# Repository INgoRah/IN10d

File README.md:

Arduino 1-Wire Homeautomation Base

# Changes
[x] timer based control (different switch table?). Use CLI sw t <bus> <adr> <latch> <bus> <adr> <pio>.
    Default 30 secs at the moment
[x] Host IF for switch table
[x] Host IF for control
[x] Host GPIO signal verified
[x] Switch with same dst does not clear timer if running.
[x] Log latch and switch

# Documentation

## Build
Create a post_extra_script.py to copy over to PI:
Import("env", "projenv")
env.AddPostAction(
    "$BUILD_DIR/${PROGNAME}.elf",
    env.VerboseAction(" ".join([
        "scp ",
        "$BUILD_DIR/${PROGNAME}.hex", "<user>@<ip>:<path>/${PROGNAME}.hex"
    ]), "Copying $BUILD_DIR/${PROGNAME}.hex")
)

Build using PlatformIO: %USERPROFILE%\.platformio\penv\Scripts\platformio.exe run --environment nanoatmega328-deploy

Debugging with "simulation" target

## Features Details

### Alarm handling

Each custom DS2408 generates an alarm signal of > 800 us on the OneWire line. No
other master supports detection of it. But this is a feature of the iButton.
Therefore I need a master to at least monitor the line and signal it to an
other master. The Arduino turned out to be fast and stable to handle basic
light switches in reasonable time compared to a Linux host (threads, updates,
script latency and overhead). So the Arduino controls the light switches.

### Address format and limitations

The adress scheme is aligned with the slave implementation to save space in
the Arduino Nano and speed up the lookup. Only bus and address needs to be known
(and detected in the alarm search).
The latch in the lookup table is only the latch number, no bitmap. Means pressing two
switches at the same time is ignored (first latch taken).

Slaves are based on the OneWireSlave Attiny code uses a format like this:
29 | id | bus | ~id | ~bus | 66 | 77 | CRC
with id: 0 .. F
PIO0/1 are output (usually, but can be configured)
Latch2..7 are input (usually)
A special destination type for other devices (like DS2413) is reserved.
The custom DS2408 implementation also serves a alarm signal of 900 us like
the iButtons do. This avoids frequent polling (would need to be around 200 ms)

### Switching examples ###

A button is pressed. The slave generates an alarm signal on the bus and the Arduino
detects the long signal (> 800 us). It starts polling using the alarm condition
for the (or all) slaves in alarm condition. Reads out the registers and
starts a lookup in the timer table and switch table for commands.

### Measures to overcome limitations

Still the lookup table could be too large and this needs to be mitigated.
- fixed or stable switches in program space: easy to access via different table
  or use custom bootloader for flash storing option
- lookup in EEPROM: cache EEPROM or create new look up table (bus|adr = 4 x 31 lines returns dst by latch index),  max 1 KB

## CLI examples

## I2C format
C3 - channel select like in DS2482
F0 - reset
69 - mode selection: [2] [4]
5A - search first device, wait for search cycle for reading, returns 0 if nothing found or | id | adr [8]
5B - search next device, returns 0 if nothing found or | id | adr [8]
01 - read one event from fifo, status: busy,ok,no_data
02 - add switch entry:  type, bus, adr1, latch, press [0..2], da.bus,da.adr,da.pio
03 - write PIO: type, bus, adr1, pio and release lock, check for an event acknowledging the change
E2 - lock i2c bus and get status, if no events in the queue the lock is released again
78 - Handle ack: pass the sequence number to be acked, this releases the lock

status: alarm bus 3 | alarm bus 2 | alarm bus 1 | alarm bus0
bus select
read out alarm : adr | latch
read out status : write adr | read PIO

### Host Communication

On GPIO low, read status register
Set read pointer:
    Write 0xE1 0xE1
Read one byte (status)
If event data (0x40)
    write 0x1
    status changes to BUSY, wait for OK or NO_DATA
    on ok send read data request
    write 0x96
    read data (on event 9 bytes): type, bus, adr, latch, press, 16 bit data, seq, 0xaa
    seq: 1..0x7f
    read status again and repeat if needed

### Handling events Implementation details:
- check alarm status which resets the gpio, ALARM_STATUS_REGISTER
   iic.i2cWriteSync(iicAdr, 2, Buffer.from([0xE1, 0xA8]));
- read one byte and check for 0x40 otherwise cancel
- request event data, selects status register
  The controller copies the data over from the fifo
  Send CMD_EVT_DATA (= 0x1)
    iic.i2cWriteSync(iicAdr, 1, Buffer.from([0x1]));
    release the bus iic.closeSync();
- read status in a loop till 0
    0 = ok, data is prepared
    1 = busy/waiting to read data
    0x80 no data: return
- select data register, status is READY = 0x4
    iic.i2cWriteSync(iicAdr, 1, Buffer.from([0x96]));
    delay...?
    iic.i2cReadSync(iicAdr, 9, rbuf);
    rbuf[7] contains the sequence number
- send ack
    This will clear the fifo entry and increases the sequence number.
    This also may release the I2C host bus
    iic.i2cWriteSync(iicAdr, 2, Buffer.from([0x78, rbuf[7]]));

### sending commands details
    set read ptr to DS2482_STATUS_REGISTER
    iic.i2cWriteSync(iicAdr, 2, Buffer.from([0xE1, 0xE1]));
    delay(1);
    // wait for ready
    do {
        iic.i2cReadSync(iicAdr, 1, rbuf);
        delay(1);
    } while (rbuf[0] != 0);

    iic.i2cWriteSync(iicAdr, 5, Buffer.from([0x3, bus, id, pio, <level>]));

## Switch configuration

sw : dumps the table
sw r : reads the table from eeprom again
sw s : saves the table into eeprom
sw c : clears the table
sw d <bus> <adr> <latch>: deletes a switch
sw s <bus> <adr> <latch> <dst bus> <dst adr> <dst pio> [type]
	add a switch
sw t <timer type> <bus> <adr> <latch> <dst bus> <dst adr> <dst pio> [type]
	Add a timed switch
    Timed table	timer type: 1 = 20 sec, 2: 30 sec, 3: 1 min, 4: 2 min, 5: 5 mins ...
    Timer on darkness: offset 10
	Timer on darkness with soft off per time if supported (dimmable), time 5 secs: offset 20

    latch 10 .. 17: long press
    latch 0 .. 7: normal press
    latch 20 .. 27: pressing

## EEPROM config space

3 6 0 1 0 0 3 0 80 1D 9 2
            vers=3 tbl@8 len=3
	                timed  @15 timed vers=2 len=0 / Max 40
			       16bit @ 17 vers=0 len=0 / Max 0

start:
pin 0 2 0 20 1 240
pin 2 7 0 60 1 250
pin 0 4 5 40 2 90
stop
pin 0 2 0 eb 0 0
pin 0 2 0 ee 0 0
on
pin 0 2 0 DD 0 254
pin 2 7 0 DD 0 254
off
pin 0 2 0 EB 0 0
pin 2 7 0 EB 0 0

brightness
pin 2 7 0 e3 250 0
pin 0 2 0 e3 250 250

threshold
pin 2 7 0 e5 236 0
pin 0 2 0 e5 240 0

cfg 7 w ff ff ff ff 20 ff ff ff ff ff ff 23 02 00 00 ff ff ff ff FC
             DD
          E4 20 0 A 6 4
cfg 7 w 1 e4 28 0 0 3 3 0 21 0 0 0 0 0 0
= level = 200
= time = 2 min
cfg 2 w 1 D0 30 0 A 3 3 0 21 0 0 0 0 0 0

        R |R |R |SW 1  2  3  4  5  6  7 |CFG 1 2  3  4  5  6  7 |FEA|OFF|MAJ|MIN|TYP
cfg 2 w F8 FF FF FF FF FF FF FF 20 FF FF 23 21 21 21 21 02 10 10
        T|TH|DD|DU|DF|T1|T2|SW 1  2  3  4  5  6  7
cfg 2 w 1 C0 20 00 0A 03 01 ff ff ff FF FF 21 FF FF FF FF FF FF
cfg 2 w 1
cfg 2

cfg 7 w 1
        T|TH|DD|DU|DF|T1|T2|SW 1  2  3  4  5  6  7
cfg 7 w 1 40 10 00 0A 01 01 FF 21 FF FF FF FF FF FF FF FF FF FF FF FF
p 2 7 0 30

cfg 7 w ff ff ff ff 20 ff ff ff ff ff ff 23 02 21 02 ff ff ff ff FC
cfg 1 w ff ff ff ff ff ff ff ff ff ff ff 02 02 02 02 ff ff ff ff FC

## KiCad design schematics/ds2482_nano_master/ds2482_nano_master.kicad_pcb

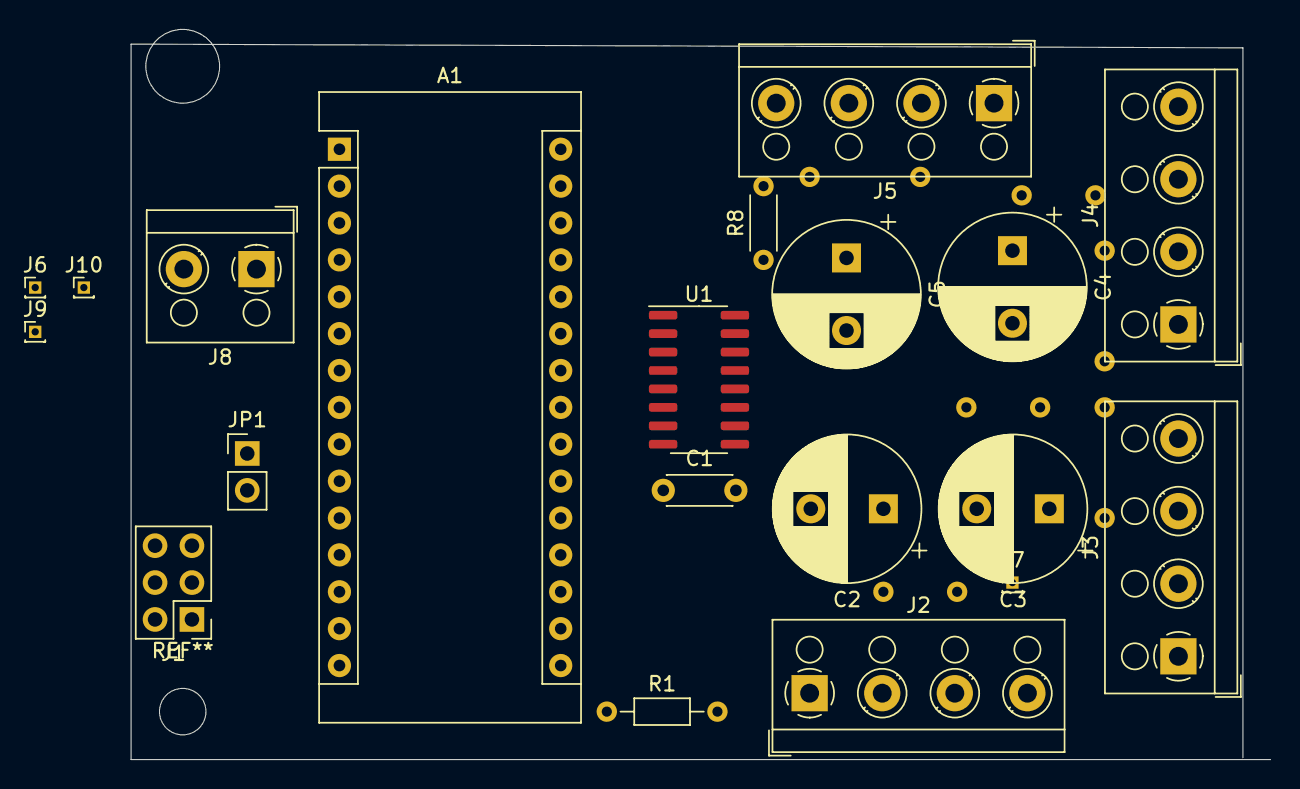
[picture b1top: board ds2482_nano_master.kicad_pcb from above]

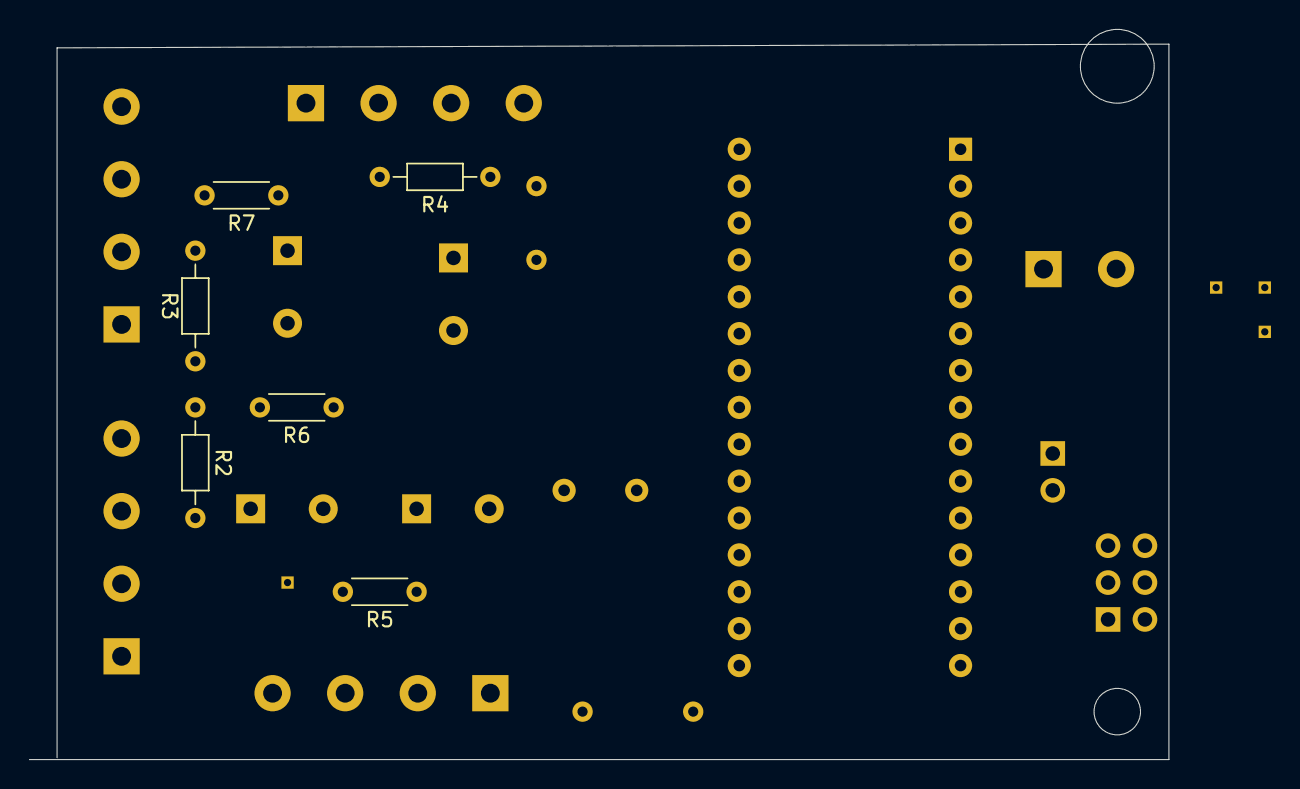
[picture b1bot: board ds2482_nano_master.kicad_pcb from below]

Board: 2 copper layers, 78.5 x 50.3 mm, 26 parts (6 on the bottom side), 22 nets, no tracks yet.

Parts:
A1: Arduino_Nano_v3.x; Arduino_Nano
C1: 220nF; C_Disc_D4.3mm_W1.9mm_P5.00mm
C2, C3, C4, C5: 1000uF; CP_Radial_D10.0mm_P5.00mm
J1: Conn_02x03_Top_Bottom; PinHeader_2x03_P2.54mm_Vertical
J2, J3, J4, J5: Screw_Terminal_01x04; TerminalBlock_RND_205-00003_1x04_P5.00mm_Horizontal
J6, J7, J9, J10: Conn_01x01; PinHeader_1x01_P1.00mm_Vertical
J8: Screw_Terminal_01x02; TerminalBlock_RND_205-00001_1x02_P5.00mm_Horizontal
JP1: Jumper; PinHeader_1x02_P2.54mm_Vertical
R1, R2, R3, R4: 10; R_Axial_DIN0204_L3.6mm_D1.6mm_P7.62mm_Horizontal
R5, R6, R7, R8: R; R_Axial_DIN0204_L3.6mm_D1.6mm_P5.08mm_Horizontal
U1: DS2482-800; SOIC-16_3.9x9.9mm_P1.27mm

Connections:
+5V: A1.27, C1.1, J8.2, R1.1, R2.1, R3.1, R4.1, U1.4
ALARM: A1.9, J1.5
GND: A1.4, C1.2, C2.2, C3.2, C4.2, C5.2, J1.4, J2.1, J3.1, J4.1, J5.1, J8.1, U1.6, U1.7, U1.8, U1.13
IO0: A1.19, R5.1, U1.14
IO1: A1.20, R6.1, U1.15
IO2: A1.21, R7.1, U1.16
IO3: A1.22, R8.1, U1.1
unnamed: C2.1, J2.2, R1.2
unnamed: C3.1, J3.2, R2.2
unnamed: C4.1, J4.2, R3.2
unnamed: C5.1, J5.2, R4.2
unnamed: J1.2, JP1.2
unnamed: J2.3, R5.2
unnamed: J2.4, J7.1
unnamed: J3.3, R6.2
unnamed: J3.4, J6.1
unnamed: J4.3, R7.2
unnamed: J4.4, J9.1
unnamed: J5.3, R8.2
unnamed: J5.4, J10.1
SCL: A1.24, J1.3, U1.2
SDA: A1.23, J1.1, U1.3

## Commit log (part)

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2020-07-03 initial repo creation
2020-07-03 first switcher version
2020-07-03 Initial files and libs
2020-07-03 CLI and device handling split
    search via I2C
2020-07-03 Switch matrix drafted
2020-07-09 Add Schematic
2020-07-09 Add missing files update readme
2020-08-30 Split of TWI host and Watchdog
    Channel addressing (WIP)
    Switch table from EEPROM
    Adress scheme change
2020-09-06 multi bus implemented
2020-11-13 temperature experiments
    host update queue
2020-11-23 New dataformat for source switches
2020-12-07 Refactoring and new features
    - timed switches (currently default time 15 secs)
    - long press detection (pressing and press)
    - dimmer (PWM devices)
2020-12-09 Added logging feature
    PIR sensor directly at PD2 / D2
2021-01-19 some clean up
    host interface started to optimize
    switch level handling
2021-01-23 Adding change ID command
2021-01-23 Clean up host interface (ongoing)
    Introduce main header
    Minor optimizations
2021-04-22 Ongoing switch handling
2021-04-22 Class optimization and host interface improvements
    Fix for missing I2C data: need copy the data in event callback
    unit tests for switch cases
2021-04-22 Host interface improvements
2021-04-22 remove files from repo
2021-11-02 Adds Light sensor based switching
2021-11-02 Improvements
    - Class optimization
    - Added larger PIO union for more pios in addition
    to the 8 bit destination incl. mapping
    - own pins extended with adr #9:pin (except pin 5 = pio0 for PWM)
    - lots of host interface improvements (WIP)
    - improved unit tests
2021-11-02 CLI improvements
    - Add bus parameter on p (pio) and s (status) commands
    - Set level to 100 if input is 1
2021-11-02 Host Interface WIP
2021-11-02 Handle multiple latch bits as on auto switching now
    latch and the output is signaled
2021-11-02 Soft (for dimmer) off and other timer types/times. Now timers are also supported if not dark
    CLI remembers bus and address for pio and status commands
    Adds a configurable light threshold and a max dimmer on level (possible to limit in the night)
    Other cleanup and optimizations
2021-11-02 Optimizations
2021-11-02 CLI improvements
    use global bus and adr if not specified make shorter inputs possible
2021-11-02 Lots of clean up
    dim stage correction for internal PWM
    Add two pins of internal controller for PIR and state
    Soft dim down on switching on (nice demo feature)
2021-11-03 Add a pre script to generate a version based on the last git tag
2021-11-03 fixes
2021-12-10 Caching of PIO to speed up switching
    Saves time for reading the PIO via 1-wire
2021-12-13 Adding humidity on fake DS1820 (with DHT22)
2022-01-07 Bug Fixes
2022-07-19 Power Interval support
2022-07-19 more for power
2022-07-21 minor code clean up / improvements
2022-07-21 I2C timeout handling 1st
2022-07-21 I2C timout 2nd
2022-07-25 Lets include the hash for version prints
2022-12-28 set host alarm by alarmHandler only
    printing optimizations
2022-12-29 Improved error handling
2022-12-29 Error improvements and ch cache
2022-12-31 Error handling improve (3)
2023-01-17 logging improvements
2023-03-25 Power Interval support Minor code clean up / improvements
2023-03-25 Set host alarm by alarmHandler only Stability and robostness on low level OneWire handling Channel cache
2023-03-25 Logging and error handling improvements Stability and robostness on low level OneWire handling
2023-03-25 SW Host lock cacheInit and initial states (for timer IO) in case of reboot
2023-03-28 Productive compile switch to reduce memory
2023-09-09 Add new pin header for output control
2023-10-01 internal PIOs improvements and doc
2023-10-02 minor
2023-10-02 fixed power pin
2024-11-18 initial RP2040 support with Ethernet and MQTT
2024-11-22 New eeprom layout
    Support storing mode, debug and some configs
    Add a CLI for new extended pins
    Preparations for 16 destination IOs
    Final change with addition variables in EEPROM and 16 bit dst table preparation
2024-11-25 New pin level and timer set support Draft external ADC (for light) support and auto switch brightness setting
2025-11-17 Disable soft off support Add ADC read out from DS2450 chips Change intern adr to 0 (and bus stays 0) - no longer used
2025-11-17 Optimizations
    - cleanup
    - printouts and debug levels
2025-11-18 Add simply pio run CI test
    Fix exception in pre_script.py
    Add post script sample
2025-11-18 Refactoring, optimization, cleanup
2025-11-18 Add ADC read out from DS2450 chips
    Change intern adr to 0 (and bus stays 0) - no longer used
    Optional compile in intern PIOs
    Disable soft off support
2025-11-18 Draft 16 bis dst table
2025-11-18 Init devices version and update selected ones
    debug levels and watchdog
2026-06-02 optimize params and debugging setlevel
2026-06-02 Add 1w log buffer and dump
2026-06-02 host interface optimizations Host mode settings and status bits
2026-06-02 Watchdog optimizations
2026-06-02 fix version check and light loop
2026-06-02 Optimize host interface
